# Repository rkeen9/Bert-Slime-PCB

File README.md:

# Bert-Slime-Tracker
**DOES NOT WORK YET.** If you build this, you will get a non-functional tracker. This repository will be updated once troubleshooting is complete. I'm documenting the troubleshooting here: [Troubleshooting](https://github.com/rkeen9/Bert-Slime-Tracker/blob/main/Troubleshooting/Troubleshooting.md)

Another slime tracker. This one was designed for small form factor and easy DIY that involves minimal soldering and easily obtainable parts. This is essentially just an ICM-45686 breakout board which you can install a D1 mini directly to via 2x8 port 2.54 mm female headers. A TP-4056 charger module can also be installed directly to the board via 2.54mm male headers. Assembly instructions to come once this project is functional.

# Folder Structure 
- **Bert-Slime-Tracker/** Main folder. Contains KiCAD project files and all other folders.
- **Bert-Slime-Tracker/Libraries** Contains all custom symbols and footprints used in this project
- **Bert-Slime-Tracker/assembly-files** Contains all files that would be needed to have this project built by JLCPCB (https://jlcpcb.com/).
- **Bert-Slime-Tracker/Schematics** Contains the schematic in PDF form.
- **Bert-Slime-Tracker/Troubleshooting** Contains my efforts to get this project functional :).

# KiCAD Environment Setup
This project was made in KiCAD 9.0. KiCAD is free PCB design software which can be downloaded from https://www.kicad.org/download/. If you are familiar with KiCAD and Github, all you need to know is that the required files for all custom components are in the **Libraries** folder.

If you're new to KiCAD or need a refresher, the following is step by step instructions for opening this project following a fresh KiCAD install:
1. Download this project through GitHub's **Download Zip** option as shown below and extract it to the desired project location:

2. Run KiCAD and open the **Footprint Editor** from the start screen

Continue with the default options if this popup appears:

3. From the **Footprint Editor**, Go to **File>Add Library**

Navigate to where you extracted the project files, select the **Libraries/Bert-Slime-PCB.pretty** folder, and hit **Select Folder**

4. Exit from the **Footprint Editor** and open the **Symbol Editor** from the KiCAD start screen

Continue with the default options if this popup appears:

5. From the **Symbol Editor**, Go to **File>Add Library**

Navigate to where you extracted the project files and open the **Libraries/Bert-Slime-PCB.kicad_sym** file.

6. Exit from the **Symbol Editor** and open the project from the KiCAD start screen as shown:

Now navigate to the project folder and open the **bert_slime_tracker.kicad_pro** file

7. The project can now be edited in KiCAD. the **bert_slime_tracker.kicad_sch** file contains the project schematics and the **slime_tracker.kicad_pcb** file contains the PCB design itself.

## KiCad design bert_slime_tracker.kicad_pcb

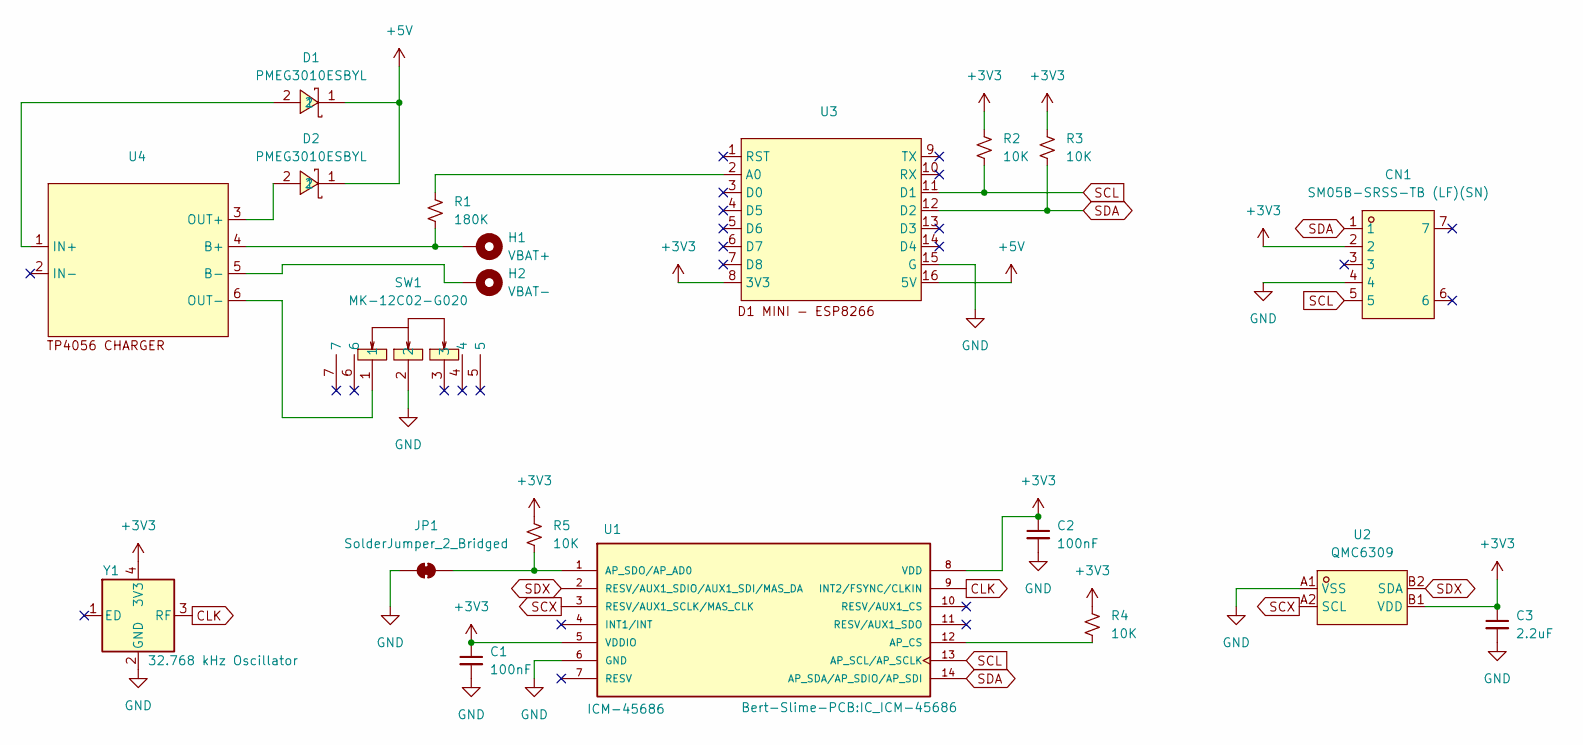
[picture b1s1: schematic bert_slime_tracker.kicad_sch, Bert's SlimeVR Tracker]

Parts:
C1, C2: 100nF; C_0603_1608Metric; LCSC Part C1591
C3: 2.2uF; C_0603_1608Metric; LCSC Part C57895
CN1: SM05B-SRSS-TB (LF)(SN); CONN-SMD_SM05B-SRSS-TB-LF-SN; LCSC Part C136657
D1, D2: PMEG3010ESBYL; SOD993_L1.0-W0.6-LS1.0-RD; LCSC Part C458181
H1: VBAT+; TestPoint_Pad_2.0x2.0mm
H2: VBAT-; TestPoint_Pad_2.0x2.0mm
JP1: SolderJumper_2_Bridged; SolderJumper-2_P1.3mm_Bridged_Pad1.0x1.5mm
R1: 180K; R_0603_1608Metric_Pad0.98x0.95mm_HandSolder; LCSC Part C22827
R2, R3, R4, R5: 10K; R_0603_1608Metric_Pad0.98x0.95mm_HandSolder; LCSC Part C25804
SW1: MK-12C02-G020; SW-SMD_MK-12C02-G020; LCSC Part C963206
U1: ICM-45686; IC_ICM-45686; PARTREV 0.2; LCSC Part C22459454
U2: QMC6309; X1-WLB0808-4_L0.8-W0.8-P0.40-TL; LCSC Part C5439871
U3: D1-Mini
U4: TP4056-USBC-MODULE
Y1: 32.768 kHz Oscillator; Crystal_SMD_3225-4Pin_3.2x2.5mm; LCSC Part C555607

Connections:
+3V3: C1.1, C2.1, C3.1, CN1.2, R2.1, R3.1, R4.1, R5.1, U1.5 (VDDIO), U1.8 (VDD), U2.B1 (VDD), U3.8 (3V3), Y1.4 (3V3)
+5V: D1.1, D2.1, U3.16 (5V)
CLK: U1.9 (INT2/FSYNC/CLKIN), Y1.3 (RF)
GND: C1.2, C2.2, C3.2, CN1.4, JP1.1 (A), SW1.2, U1.6 (GND), U2.A1 (VSS), U3.15 (G), Y1.2 (GND)
unnamed: JP1.2 (B), R5.2, U1.1 (AP_SDO/AP_AD0)
unnamed: R4.2, U1.12 (AP_CS)
unnamed: R1.2, U3.2 (A0)
unnamed: H1.1, R1.1, U4.4 (B+)
unnamed: H2.1, U4.5 (B-)
unnamed: D1.2, U4.1 (IN+)
unnamed: D2.2, U4.3 (OUT+)
unnamed: SW1.1, U4.6 (OUT-)
SCL: CN1.5, R2.2, U1.13 (AP_SCL/AP_SCLK), U3.11 (D1)
SCX: U1.3 (RESV/AUX1_SCLK/MAS_CLK), U2.A2 (SCL)
SDA: CN1.1, R3.2, U1.14 (AP_SDA/AP_SDIO/AP_SDI), U3.12 (D2)
SDX: U1.2 (RESV/AUX1_SDIO/AUX1_SDI/MAS_DA), U2.B2 (SDA)

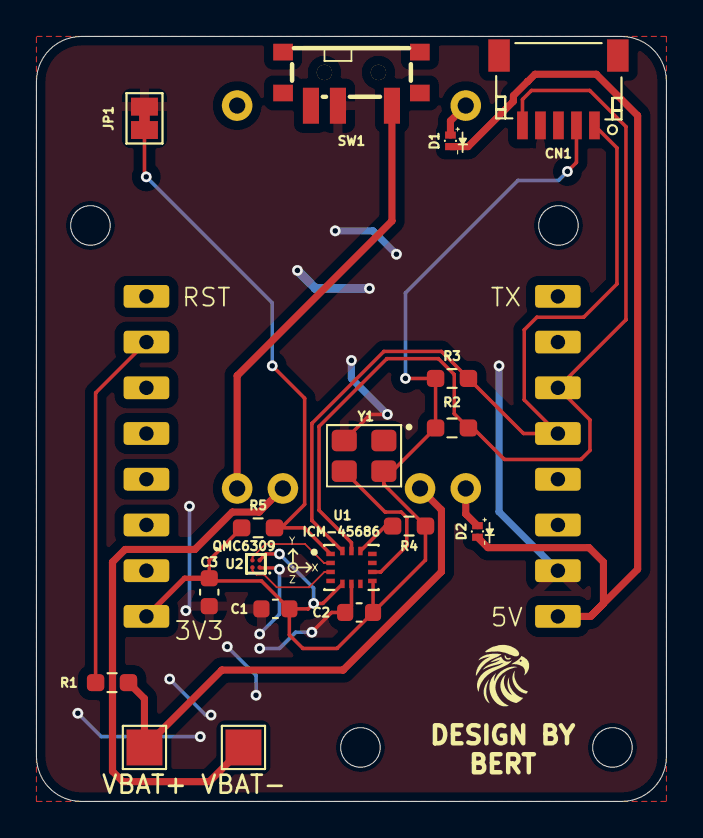
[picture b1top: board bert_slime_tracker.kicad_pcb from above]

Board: 2 copper layers, 35.0 x 42.5 mm, 20 parts (0 on the bottom side), 16 nets.

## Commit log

2025-06-27 Converted from global to project libraries
2025-06-27 added license
2025-06-27 added photos for environment setup and modified file names
2025-06-27 added gitignore
2025-06-27 removed backup folder
2025-06-27 modified image names
2025-06-27 Update LICENSE
2025-06-28 added schematic files
2025-06-28 added some images and a troubleshooting folder
2025-06-28 added more troubleshooting info
2025-06-28 added some documentation for my troubleshooting
2025-06-28 fixed troubleshooting doc formatting
2025-06-28 updated to corrected oscillator
